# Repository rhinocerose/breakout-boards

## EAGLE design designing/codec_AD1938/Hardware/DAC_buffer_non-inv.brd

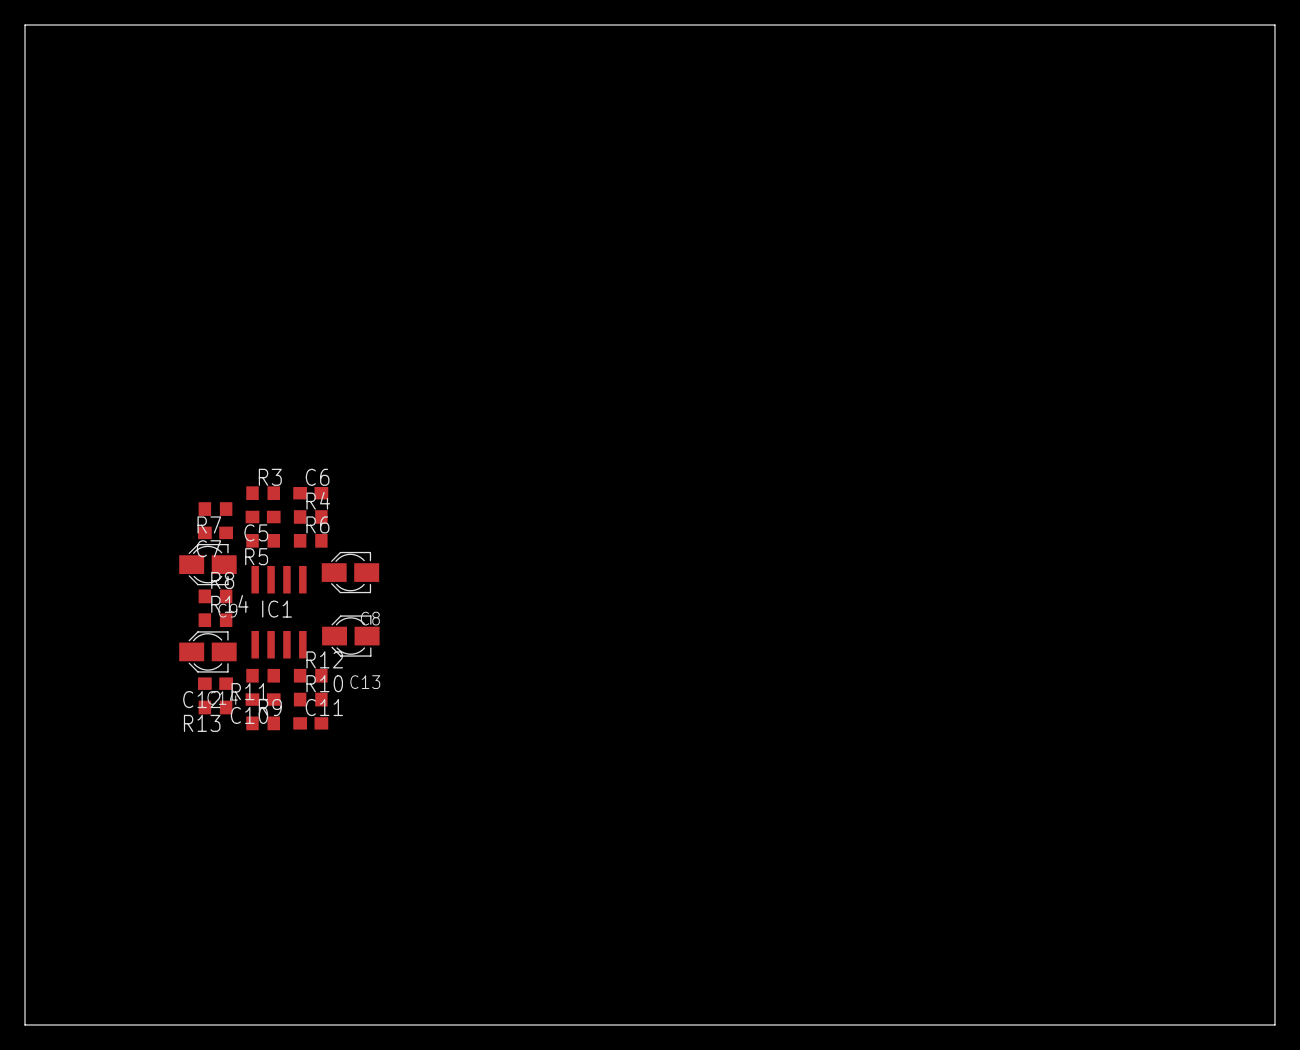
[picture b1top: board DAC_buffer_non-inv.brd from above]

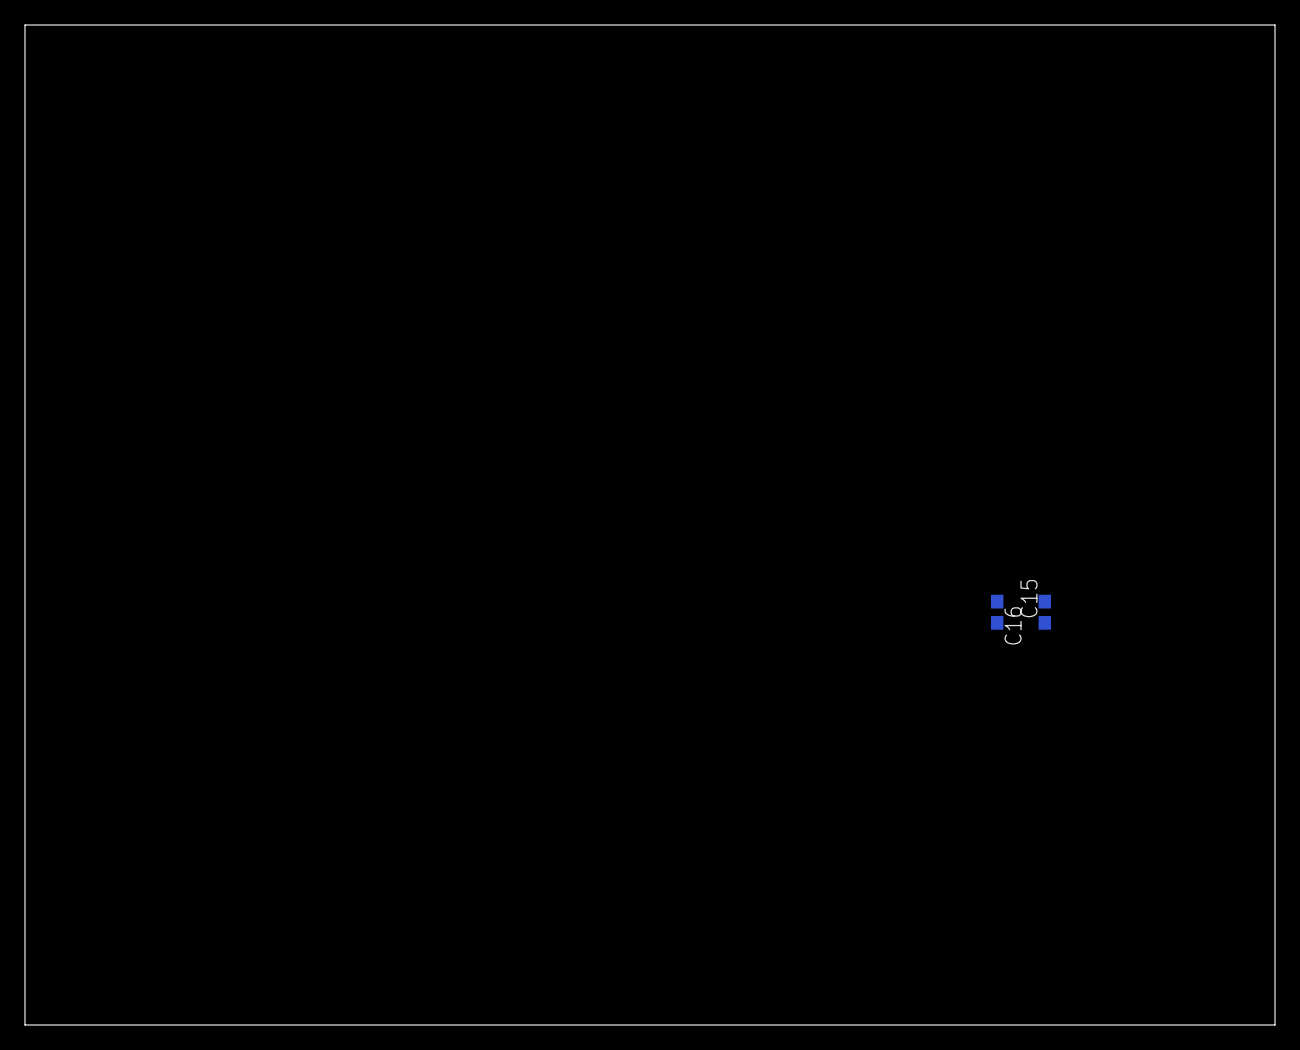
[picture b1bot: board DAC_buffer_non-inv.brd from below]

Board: 2 copper layers, 100.0 x 80.0 mm, 25 parts (2 on the bottom side), 17 nets, no tracks yet.

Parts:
C5, C10: 270pF; C0603
C6, C11: 430pF; C0603
C7, C12: 2.2nF; C0603
C8, C9, C13, C14: 47uF; PANASONIC_A
C15, C16: 100nF; C0603
IC1: TL072D; SO08
R3, R4, R5, R6, R9, R10, R11, R12: 4k75; R0603
R7, R13: 100R; R0603
R8, R14: R0603

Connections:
+12V: C15.2, IC1.8
-12V: C16.2, IC1.4
AGND: C6.1, C7.1, C8.-, C11.1, C12.1, C13.-, C15.1, C16.1, R8.1, R14.1
unnamed: C5.1, R3.2, R4.1
unnamed: C6.2, IC1.5, R4.2
unnamed: C5.2, IC1.7, R5.2, R7.1
unnamed: IC1.6, R5.1, R6.1
unnamed: C7.2, C9.+, R7.2
unnamed: C9.-, R8.2
unnamed: C8.+, R6.2
unnamed: C10.1, R9.2, R10.1
unnamed: C11.2, IC1.3, R10.2
unnamed: C10.2, IC1.1, R11.2, R13.1
unnamed: IC1.2, R11.1, R12.1
unnamed: C12.2, C14.+, R13.2
unnamed: C13.+, R12.2
unnamed: C14.-, R14.2

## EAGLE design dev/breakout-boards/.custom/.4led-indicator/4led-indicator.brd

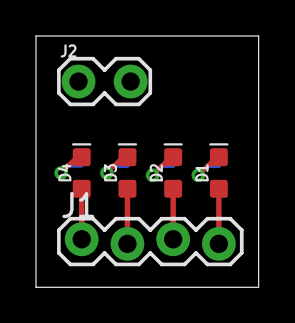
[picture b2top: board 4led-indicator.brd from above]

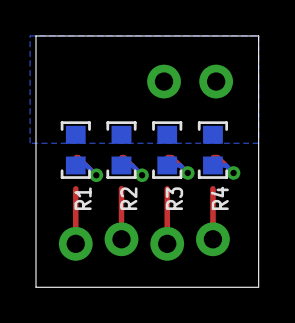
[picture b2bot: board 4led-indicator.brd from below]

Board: 2 copper layers, 12.4 x 14.0 mm, 10 parts (4 on the bottom side), 9 nets.

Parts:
D1, D2, D3, D4: LED-0603
J1: 1X04_LOCK
J2: 1X02_LOCK
R1, R2, R3, R4: R0603

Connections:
GND: J2.1, J2.2, R1.1, R2.1, R3.1, R4.1
unnamed: D1.A, J1.4
unnamed: D2.A, J1.3
unnamed: D3.A, J1.2
unnamed: D4.A, J1.1
unnamed: D1.C, R1.2
unnamed: D2.C, R2.2
unnamed: D3.C, R3.2
unnamed: D4.C, R4.2

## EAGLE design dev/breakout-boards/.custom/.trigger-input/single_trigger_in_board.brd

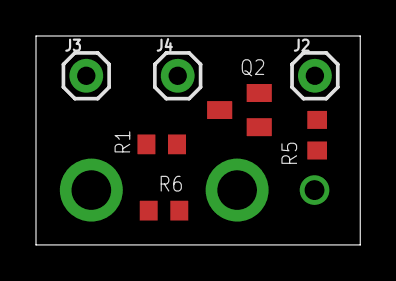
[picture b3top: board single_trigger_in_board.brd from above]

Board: 2 copper layers, 18.0 x 11.6 mm, 8 parts (1 on the bottom side), 5 nets, no tracks yet.

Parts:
J2, J3, J4: 1X01
Q2: MMBT3904LT1G; TRANSISTOR_SOT23-BEC
R1: 10k; R0603
R5: 1M; R0603
R6: 100k; R0603
TRIG1: KOBICONN_PJM301DM_JACK

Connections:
3V3_D: J3.1, R1.2
GND: J2.1, Q2.E, R5.2, TRIG1.P$2, TRIG1.P$3
unnamed: R6.2, TRIG1.P$1
unnamed: Q2.B, R5.1, R6.1
TR1: J4.1, Q2.C, R1.1

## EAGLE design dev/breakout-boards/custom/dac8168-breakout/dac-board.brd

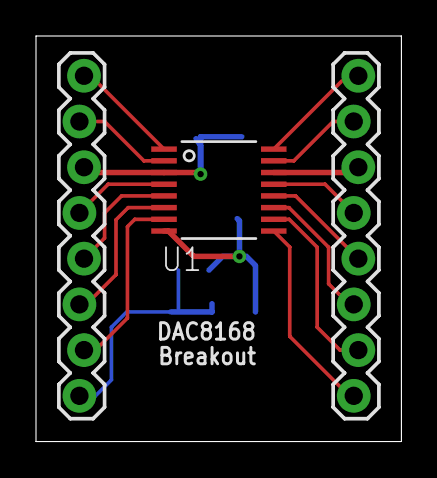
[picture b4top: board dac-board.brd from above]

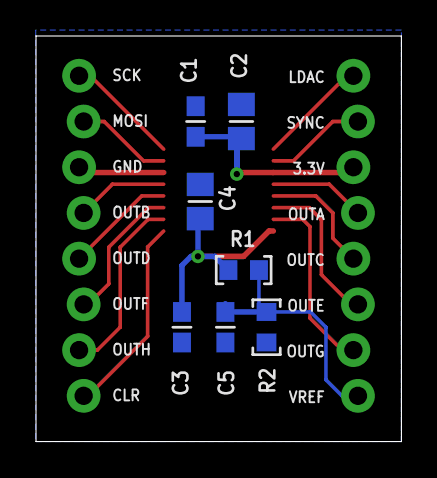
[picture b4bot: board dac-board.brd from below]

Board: 2 copper layers, 20.3 x 22.5 mm, 10 parts (7 on the bottom side), 17 nets.

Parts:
C1, C5: 100n; C0603
C2, C4: 2.2u; C0805
C3: 150n; C0603
J1, J2: 1X08_LOCK
R1, R2: R0603
U1: DAC8168ICPWPW16-L; PW16-L

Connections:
CLR: J2.1, U1.9
LDAC: J1.8, U1.1
MOSI: J2.7, U1.15
OUT_A: J1.5, U1.4
OUT_B: J2.5, U1.13
OUT_C: J1.4, U1.5
OUT_D: J2.4, U1.12
OUT_E: J1.3, U1.6
OUT_F: J2.3, U1.11
OUT_G: J1.2, U1.7
OUT_H: J2.2, U1.10
PE: C1.2, C2.2, C3.2, C4.2, C5.2, J2.6, R2.1, U1.14
SCK: J2.8, U1.16
SYNC: J1.7, U1.2
VDD: C1.1, C2.1, J1.6, U1.3
VREF: C3.1, C4.1, R1.2, U1.8
VREF_OUT: C5.1, J1.1, R1.1, R2.2

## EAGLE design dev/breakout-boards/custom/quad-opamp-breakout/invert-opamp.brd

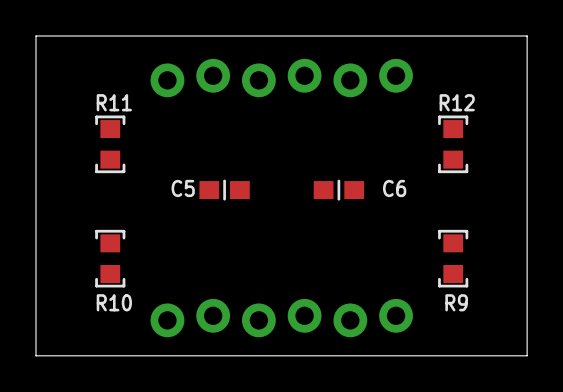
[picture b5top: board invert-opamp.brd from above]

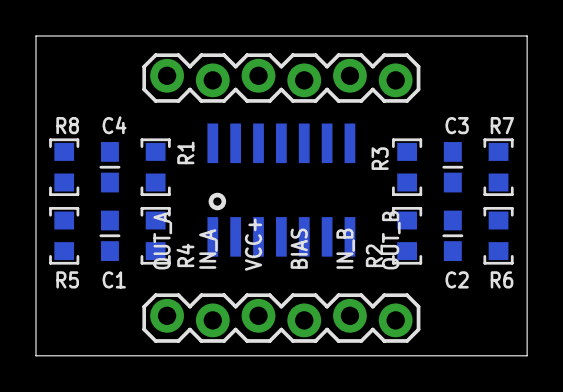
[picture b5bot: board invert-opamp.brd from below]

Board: 2 copper layers, 27.3 x 17.8 mm, 21 parts (15 on the bottom side), 20 nets, no tracks yet.

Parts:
C1, C2, C3, C4: 18pF; C0603
C5, C6: C0603
IC1: OPAMP-TL074D; SO14
J1, J2: 1X06_LOCK
R1, R2, R3, R4: 220R; R0603
R5, R6, R7, R8: 100k; R0603
R9, R10, R11, R12: 24k; R0603

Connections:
IN_A: J1.2, R9.1
IN_B: J1.5, R10.1
IN_C: J2.5, R11.1
IN_D: J2.2, R12.1
unnamed: C1.1, IC1.2, R5.1, R9.2
unnamed: IC1.1, R1.1
unnamed: IC1.8, R3.1
unnamed: C2.1, IC1.6, R6.1, R10.2
unnamed: IC1.7, R2.1
unnamed: C3.1, IC1.9, R7.1, R11.2
unnamed: C4.1, IC1.13, R8.1, R12.2
unnamed: IC1.14, R4.1
OUT_A: C1.2, J1.1, R1.2, R5.2
OUT_B: C2.2, J1.6, R2.2, R6.2
OUT_C: C3.2, J2.6, R3.2, R7.2
OUT_D: C4.2, J2.1, R4.2, R8.2
PE: C5.1, C6.2, J2.4
VCC+: C5.2, IC1.4, J1.3
VCC-: C6.1, IC1.11, J2.3
VREF: IC1.3, IC1.5, IC1.10, IC1.12, J1.4

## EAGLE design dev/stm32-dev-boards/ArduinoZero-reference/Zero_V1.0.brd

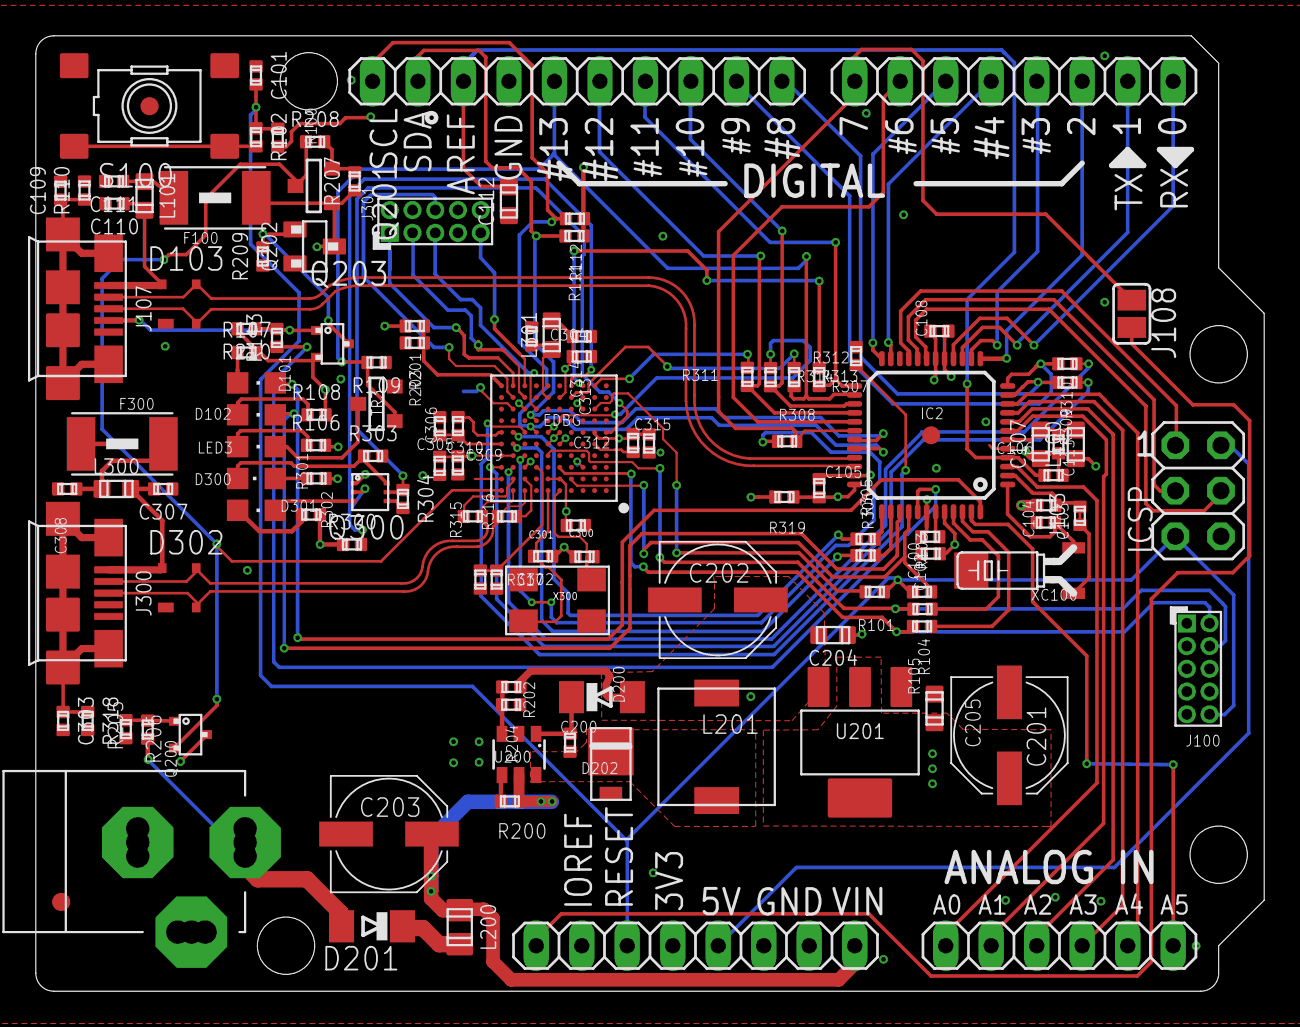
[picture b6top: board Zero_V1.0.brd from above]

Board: 4 copper layers, 68.6 x 53.3 mm, 129 parts (0 on the bottom side), 104 nets.

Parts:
C100, C101, C102, C105, C106, C108, C113, C304, C309, C311, C312, C313: 100nF; C0402
C103, C104: 6.8pF; C0402
C107: 10uF; C0603
C109, C303: DNP; C0402
C110, C111: 4.7nF; C0402
C112, C204, C205: 4.7uF; C0603
C200: 10n; C0402
C201, C203: 10uF; PANASONIC_D
C202: 47u; PANASONIC_D
C300, C301: 22pF; C0402
C302: 10pF; C0402
C305, C310: 1uF; C0402
C306, C307, C308: 1nF; C0402
C314, C315: 2.2uF; C0402
D101, D102, D301: Yellow; CHIPLED_0805
D103, D302: PRTR5V0U2XB; SOT143B
D200: CD1206-S01575; MINIMELF
D201: BYS10-45-E3; MINIMELF
D202: SS1P3L; DO220AAL
D300: Green; CHIPLED_0805
EDBG: VFBGA100
F100: MF-MSMF050-2; WUERTH-ELEKTRONIK_1812
F300: WUERTH-ELEKTRONIK_1812
FD1, FD2: FIDUCIALMOUNT; FIDUCIA-MOUNT
IC2: SAMD21G18A-AUT; TQFP48
ICSP: 3x2 M; 2X03
J100, J301: PINHEAD-2x5-P1.27; PINHEAD_2X05_127
J101: FH254-110DF08500V; 1X10
J102, J105: FH254-108DF08500V; 1X08
J103: C0402
J106: FH254-106DF08500V; 1X06
J107, J300: ZX62-AB-5PA; USB-MICRO-10103594
J108: SJ
J200: POWER-SUPPLY; POWERSUPPLY_DC-21MM
L100, L101, L300, L301: BLM18PG471SN1; C0603
L200: MH2029-300Y; C0805
L201: 10uH-SRR0604-100ML; SRR0604
LED3: Yellow; CHIPLED_0805
Q200, Q203: IRLML6402PBF; SOT323
Q201: IRLML6402PBF; SOT-23
Q202: 2N7002; SOT23
Q300: 2N7002DW-7-FNO_PAD; PWR_SC70-6L2
R100, R200, R204: 10k; C0402
R101, R103, R106, R107, R108, R109, R113, R301, R302, R305, R306, R307, R308, R309, R310, R311, R312, R313, R314: 330R; C0402
R102, R315, R316: 39R; C0402
R104, R105, R319: 0R; C0402
R110, R111, R112, R208, R303, R318: DNP; C0402
R201, R203: 47k; C0402
R202: 52.3k; C0402
R205, R206, R209, R210: 100k; C0402
R207, R300, R304: 1M; C0402
R317: 6.8k; C0402
S100: PUSHBUTTON3; TS42_4PINS
TP300, TP301: TP_SP; TP-SP
TR3: Q100; SOT-23
U200: LM2734Y; SOT23-6
U201: LDO-TS1117CW-3V3; SOT223
U$5: DNP; FRAME
X300: 12mHz-12pF-K7; CRYSTAL-5.4-3.2
XC100: 32.768kHz; CRYSTAL_TC26SMD

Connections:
+3V3: C100.1, C105.1, C108.2, C201.+, C205.2, IC2.17, IC2.36, IC2.44, J100.1, J105.2, J105.4, L100.2, Q203.3, R100.2, R106.1, R107.1, R108.1, R111.2, R112.2, R201.2, R210.1, R319.1, U201.2, U201.4
+5V: C202.+, C204.1, D200.A, F100.2, ICSP.2, J105.5, L201.P$2, Q200.2, Q201.3, Q202.3, R202.1, R207.2, U201.3
ATN: J105.1, J108.2
BD_N: D302.3, EDBG.A9, J300.D-, R315.1
BD_P: D302.2, EDBG.A8, J300.D+, R316.1
BOOST: C200.1, D200.C, U200.1
DGI_GPIO1: IC2.30, J102.8, J108.1, R308.1
DGI_GPIO2: IC2.11, J101.1, R309.1
DGI_GPIO3: IC2.12, J101.2, R310.1
EDBG_ADC0: EDBG.K10, R201.1, R203.2
EDBG_FORCE_BOOT: EDBG.H9, TP301.X
EDBG_JTAG_TCK: EDBG.K9, J301.1
EDBG_JTAG_TDI: EDBG.K8, J301.9
EDBG_JTAG_TDO: EDBG.J8, J301.3
EDBG_JTAG_TMS: EDBG.H7, J301.5
EDBG_RESET_N: EDBG.J9, J301.6
EN: R200.2, U200.4
FB: R202.2, R204.1, U200.3
GND: C100.2, C101.2, C102.2, C103.1, C104.1, C105.2, C106.2, C107.2, C108.1, C109.1, C110.1, C111.1, C112.2, C113.2, C201.-, C202.-, C203.-, C204.2, C205.1, C300.2, C301.2, C302.2, C303.1, C304.2, C305.2, C306.2, C307.2, C308.2, C309.2, C310.2, C311.2, C312.2, C313.2, C314.2, C315.2, D103.1, D202.P$2, D302.1, EDBG.B10, EDBG.C3, EDBG.C8, EDBG.E2, EDBG.E6, EDBG.F5, EDBG.F10, EDBG.H3, EDBG.H8, IC2.5, IC2.18, IC2.35, IC2.42, ICSP.6, J100.3, J100.5, J100.9, J101.7, J105.6, J105.7, J107.GND, J200.1, J200.3, J300.GND, J301.2, J301.10, Q202.2, Q300.1, Q300.4, R109.2, R110.1, R203.1, R204.2, R206.1, R209.2, R303.1, R304.1, R317.1, R318.1, S100.1, S100.2, TP300.X, TR3.2, U200.2, U201.1, XC100.P$1
MISO: IC2.28, J101.5, R311.2
MOSI: IC2.25, J101.4, R312.2
unnamed: D300.C, Q300.6, R303.2
unnamed: D301.C, Q300.3
unnamed: LED3.C, TR3.1
unnamed: R102.1, S100.3, S100.4
unnamed: C303.2, J300.SHLD1, J300.SHLD2, J300.SHLD3, J300.SHLD4, J300.SHLD5, J300.SHLD6, R318.2
unnamed: Q201.2, R207.1, R208.1
unnamed: C110.2, D103.4, J107.VBUS, L101.1
unnamed: D201.C, L200.1
unnamed: Q202.1, Q203.2, R209.1
unnamed: C106.1, C107.1, IC2.6, L100.1
unnamed: C109.2, J107.SHLD1, J107.SHLD2, J107.SHLD3, J107.SHLD4, J107.SHLD5, J107.SHLD6, R110.2
unnamed: C111.2, F100.1, L101.2
unnamed: C308.1, F300.1, L300.2
unnamed: EDBG.B9, R315.2
unnamed: EDBG.B8, R316.2
unnamed: D102.A, R108.2
unnamed: D101.A, R107.2
unnamed: LED3.A, R106.2
unnamed: C302.1, EDBG.C7, R317.2
unnamed: C301.1, EDBG.A6, X300.1
unnamed: C300.1, EDBG.A5, X300.3
unnamed: C305.1, C306.1, EDBG.E10
unnamed: C304.1, EDBG.J6, L301.2
unnamed: EDBG.K2, R311.1
unnamed: EDBG.K3, R312.1
unnamed: EDBG.J4, R313.1
unnamed: EDBG.G5, R314.1
unnamed: EDBG.C9, R310.2
unnamed: EDBG.C10, R309.2
unnamed: EDBG.D8, R308.2
unnamed: EDBG.F8, R307.2
unnamed: EDBG.E9, R306.2
unnamed: EDBG.F9, R305.2
unnamed: D300.A, R301.1
unnamed: D301.A, R302.1
PA00_XIN32: C103.2, IC2.1, XC100.2
PA01_XOUT32: C104.2, IC2.2, J103.1, J103.2, XC100.1
PA02_AIN0: IC2.3, J106.1
PA03_AREFA: C112.1, C113.1, IC2.4, J101.8
PA04_AIN4: IC2.9, J106.4
PA05_AIN5: IC2.10, J106.5
PA08_TCC0-W0: IC2.23, J102.5
PA09_TCC0-W1: IC2.14, J102.4
PA10_TCC0-W2: IC2.15, J102.2
PA11_TCC0-W3: IC2.16, J102.1
PA14_TCC0-W4: IC2.13, J102.3
PA15_TCC0-W5: IC2.24, J102.6
PA20_TCC0-W6: IC2.29, J102.7
PA27_TX_LED: D102.C, IC2.39
PA28_USB_HOST_EN: IC2.41, R113.2
PA30_SWCLK: IC2.45, R104.1
PA31_SWDIO: IC2.46, R105.2
PB02_AIN10: IC2.47, J106.6
PB03_RX_LED: D101.C, IC2.48
PB08_AIN2: IC2.7, J106.2
PB09_AIN3: IC2.8, J106.3
PB10_S4_SPI_MOSI: IC2.19, ICSP.4
PB11_S4_SPI_SCK: IC2.20, ICSP.3
PB12_S4_SPI_MISO: IC2.21, ICSP.1
POWER_LED_CTRL: EDBG.K4, Q300.2, R300.1
RXD: IC2.38, R306.1
SAMD21_RESET: EDBG.B4, IC2.40, R103.1
SCK: IC2.26, J101.6, R109.1, R313.2, TR3.3
SCL: EDBG.F7, IC2.32, J101.10, R112.1
SDA: EDBG.G7, IC2.31, J101.9, R111.1
SS: IC2.27, J101.3, R314.2
STATUS_LED_CTRL: EDBG.F1, Q300.5, R304.2
SW: C200.2, D202.P$1, L201.P$1, U200.6
SWCLK: EDBG.D6, J100.4, R104.2
SWDIO: EDBG.C5, J100.2, R105.1
TARGET_RESET: C101.1, ICSP.5, J100.10, J105.3, R100.1, R101.2, R102.2, R103.2
TARGET_RESET_SENSE: EDBG.H2, R101.1
TARGET_USB_N: D103.3, IC2.33, J107.D-
TARGET_USB_P: D103.2, IC2.34, J107.D+
TXD: IC2.37, R305.1
USB_HOST_ENABLE: J107.ID, Q203.1, R113.1, R210.2
VCC_EDBG_3V3: C309.1, C310.1, C311.1, C312.1, C313.1, C314.1, C315.1, EDBG.B5, EDBG.B6, EDBG.D9, EDBG.D10, EDBG.E5, EDBG.F2, EDBG.F6, EDBG.J5, J301.4, L301.1, R300.2, R301.2, R302.2, R319.2
VCC_EDBG_USB: EDBG.A10, F300.2, Q200.3, Q201.1, R208.2
VCC_EXT_VIN: C203.+, J105.8, L200.2, R200.1, U200.5
VDDCORE: C102.1, IC2.43
VEXT: D201.A, J200.2, R205.2
VIN_DETECT: Q200.1, R205.1, R206.2
XVCC: C307.1, D302.4, J300.VBUS, L300.1

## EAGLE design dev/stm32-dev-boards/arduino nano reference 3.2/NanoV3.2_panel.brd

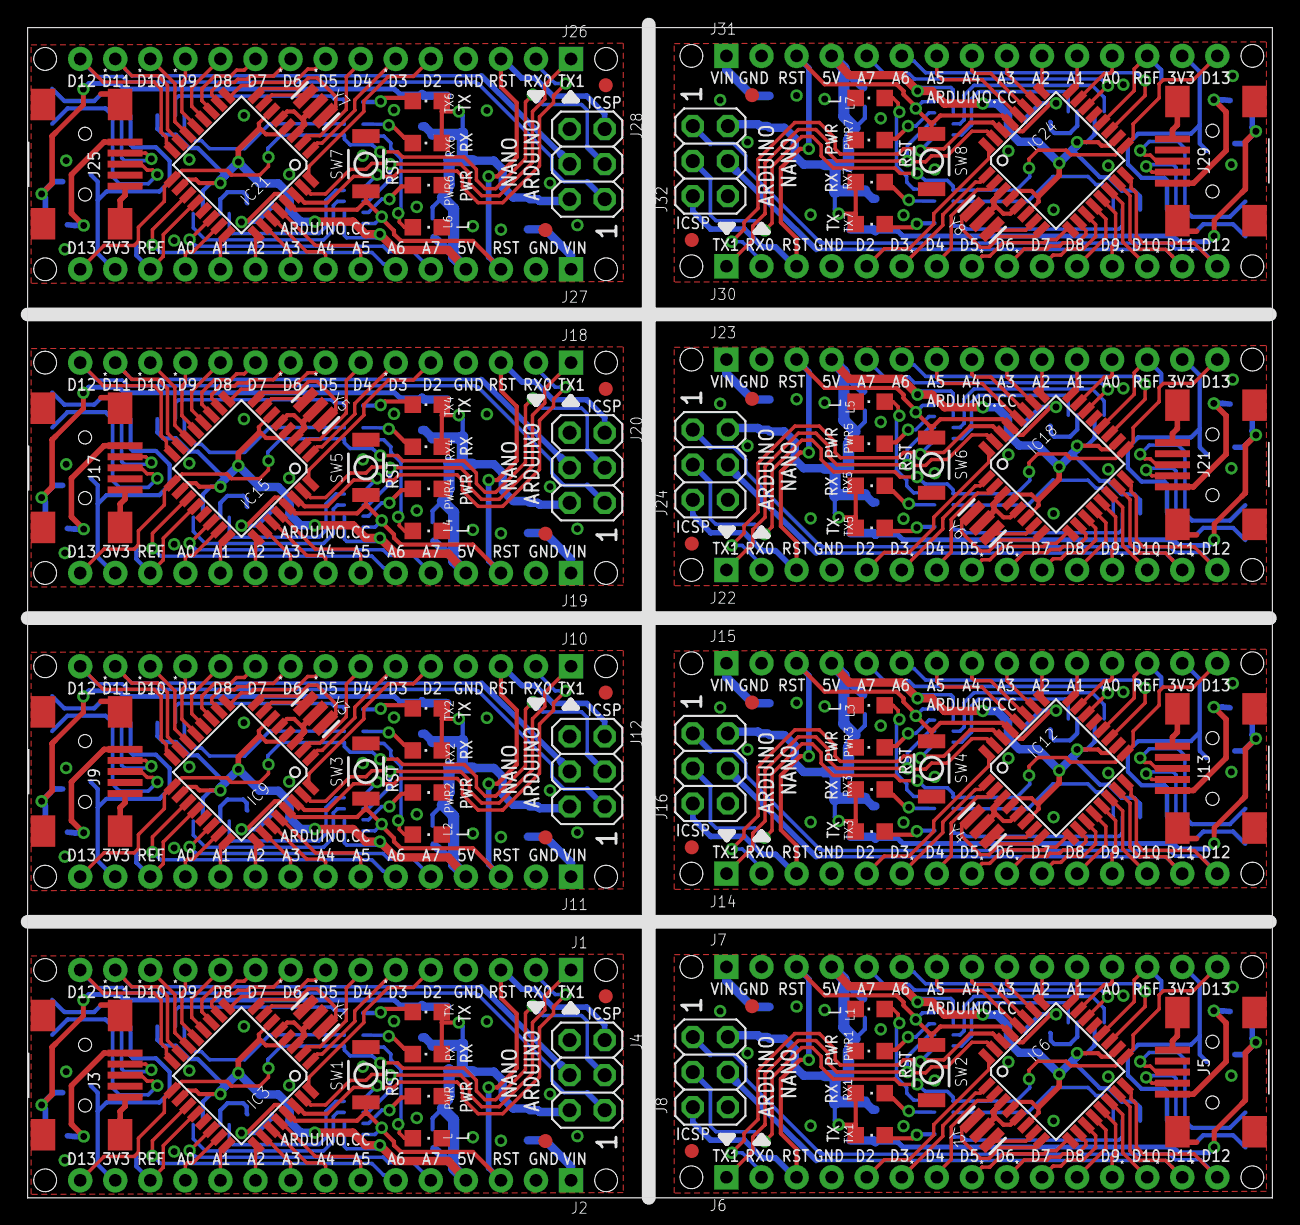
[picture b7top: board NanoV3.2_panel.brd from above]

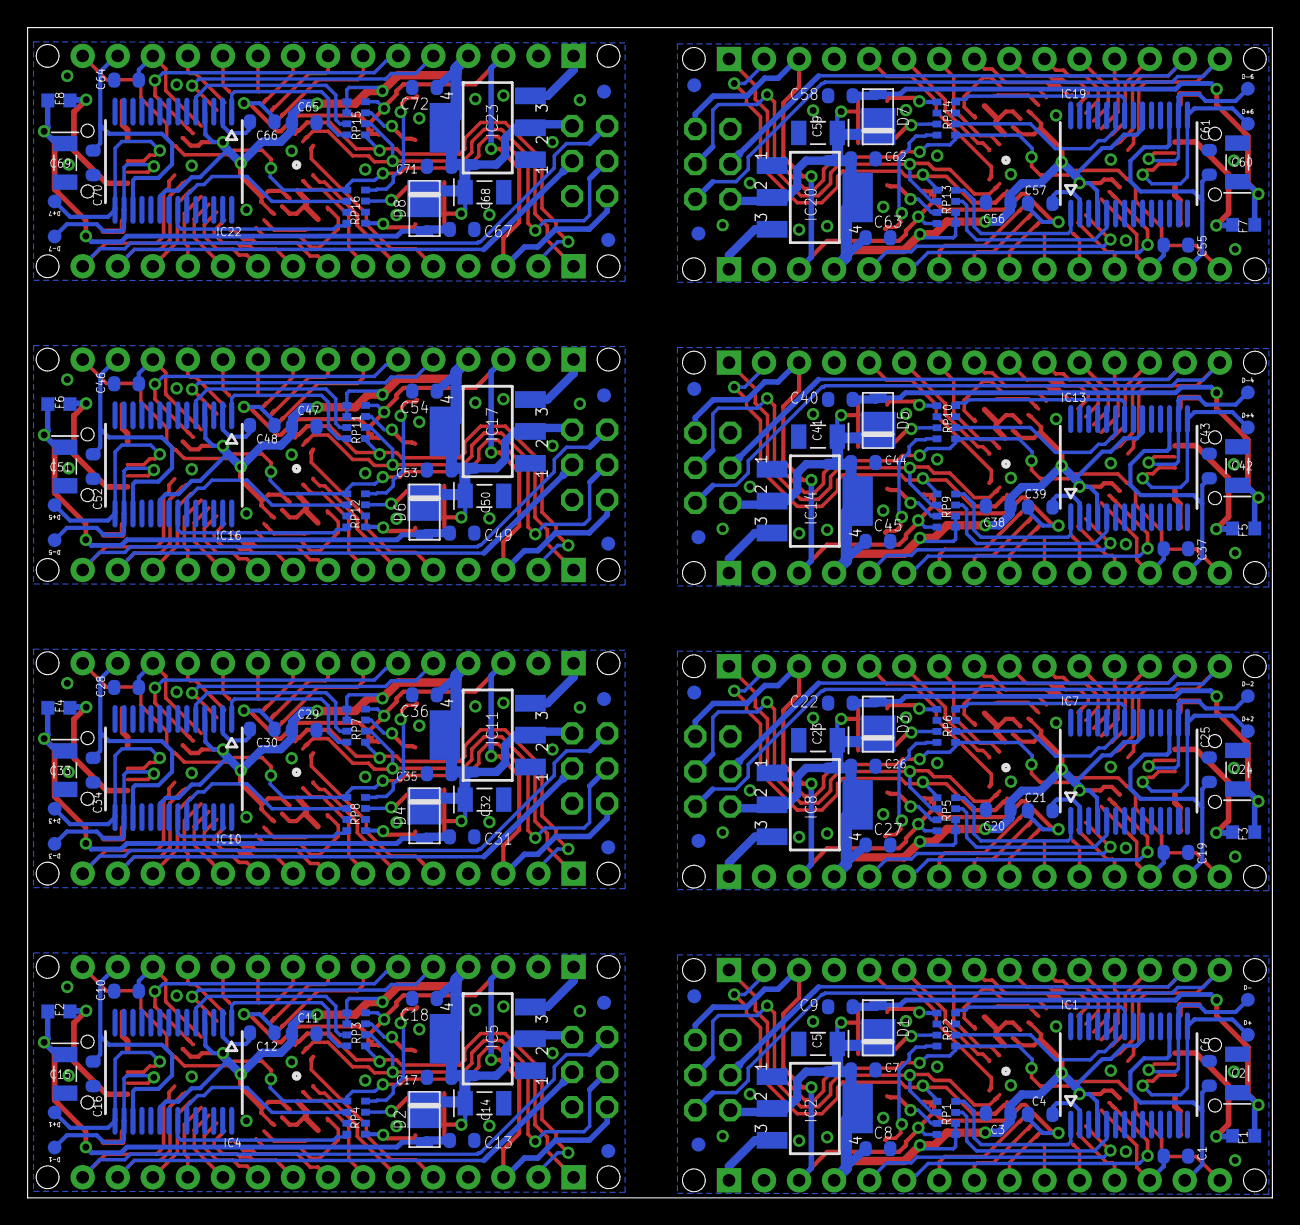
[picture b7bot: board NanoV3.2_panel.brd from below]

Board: 2 copper layers, 90.2 x 84.8 mm, 256 parts (136 on the bottom side), 344 nets.

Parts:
C1, C4, C6, C9, C10, C12, C13, C16, C19, C21, C22, C25, C28, C30, C31, C34, C37, C39, C40, C43, C46, C48, C49, C52, C55, C57, C58, C61, C64, C66, C67, C70: 100nF; C0603-ROUND
C2, C5, C14, C15, C23, C24, C32, C33, C41, C42, C50, C51, C59, C60, C68, C69: 4,7uF_16V; TAN-A
C3, C7, C8, C11, C17, C18, C20, C26, C27, C29, C35, C36, C38, C44, C45, C47, C53, C54, C56, C62, C63, C65, C71, C72: 1uF; C0603-ROUND
D1, D2, D3, D4, D5, D6, D7, D8: SS1P3L; DO220AAL
D+, D+1, D+2, D+3, D+4, D+5, D+6, D+7: DNP; TP-1.00MM
D-, D-1, D-2, D-3, D-4, D-5, D-6, D-7: DNP; TP-1.00MM
F1, F2, F3, F4, F5, F6, F7, F8: MFFSMF050; 0603-1608X90N
IC1, IC4, IC7, IC10, IC13, IC16, IC19, IC22: FT232RL; SSOP28
IC2, IC5, IC8, IC11, IC14, IC17, IC20, IC23: LM1117IMPX-5.0; LINEAR_SOT223
IC3, IC6, IC9, IC12, IC15, IC18, IC21, IC24: ATMEGA328P-AU; TQFP32-08
J1, J2, J6, J7, J10, J11, J14, J15, J18, J19, J22, J23, J26, J27, J30, J31: XXXX_STRIPNANO; HEAD15-NOSS
J3, J5, J9, J13, J17, J21, J25, J29: USB-MINI-B_2
J4, J8, J12, J16, J20, J24, J28, J32: 2X03
L, L1, L2, L3, L4, L5, L6, L7: Yellow; CHIPLED_0805
PWR, PWR1, PWR2, PWR3, PWR4, PWR5, PWR6, PWR7: Green; CHIPLED_0805
RP1, RP2, RP3, RP4, RP5, RP6, RP7, RP8, RP9, RP10, RP11, RP12, RP13, RP14, RP15, RP16: 1K; CAY16
RX, RX1, RX2, RX3, RX4, RX5, RX6, RX7: Red; CHIPLED_0805
SW1, SW2, SW3, SW4, SW5, SW6, SW7, SW8: RESET; SMD_157SW
TX, TX1, TX2, TX3, TX4, TX5, TX6, TX7: Green; CHIPLED_0805
U$1, U$2, U$3, U$4, U$5, U$6, U$7, U$8, U$9, U$10, U$11, U$12, U$13, U$14, U$15, U$16, U$17, U$18, U$19, U$20, U$21, U$22, U$23, U$24, U$25, U$26, U$27, U$28, U$29, U$30, U$53, U$54: DNP; FD-1-1.5
Y1, Y2, Y3, Y4, Y5, Y6, Y7, Y8: 16MHz; RESONATOR

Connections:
3V1: C16.2, IC4.17, J7.14
3V2: C25.2, IC7.17, J11.14
3V3: C6.2, IC1.17, J2.14
3V4: C34.2, IC10.17, J15.14
3V5: C43.2, IC13.17, J19.14
3V6: C52.2, IC16.17, J23.14
3V7: C61.2, IC19.17, J27.14
3V8: C70.2, IC22.17, J31.14
+5V: C3.1, C5.1, C7.1, C8.1, D1.P$1, IC1.4, IC1.20, IC2.2, IC2.4, IC3.4, IC3.6, IC3.18, J2.4, J4.2, RP1.5, RP1.6, RX.A, TX.A
+5V1: C11.1, C14.1, C17.1, C18.1, D2.P$1, IC4.4, IC4.20, IC5.2, IC5.4, IC6.4, IC6.6, IC6.18, J7.4, J8.2, RP3.5, RP3.6, RX1.A, TX1.A
+5V2: C20.1, C23.1, C26.1, C27.1, D3.P$1, IC7.4, IC7.20, IC8.2, IC8.4, IC9.4, IC9.6, IC9.18, J11.4, J12.2, RP5.5, RP5.6, RX2.A, TX2.A
+5V3: C29.1, C32.1, C35.1, C36.1, D4.P$1, IC10.4, IC10.20, IC11.2, IC11.4, IC12.4, IC12.6, IC12.18, J15.4, J16.2, RP7.5, RP7.6, RX3.A, TX3.A
+5V4: C38.1, C41.1, C44.1, C45.1, D5.P$1, IC13.4, IC13.20, IC14.2, IC14.4, IC15.4, IC15.6, IC15.18, J19.4, J20.2, RP9.5, RP9.6, RX4.A, TX4.A
+5V5: C47.1, C50.1, C53.1, C54.1, D6.P$1, IC16.4, IC16.20, IC17.2, IC17.4, IC18.4, IC18.6, IC18.18, J23.4, J24.2, RP11.5, RP11.6, RX5.A, TX5.A
+5V6: C56.1, C59.1, C62.1, C63.1, D7.P$1, IC19.4, IC19.20, IC20.2, IC20.4, IC21.4, IC21.6, IC21.18, J27.4, J28.2, RP13.5, RP13.6, RX6.A, TX6.A
+5V7: C65.1, C68.1, C71.1, C72.1, D8.P$1, IC22.4, IC22.20, IC23.2, IC23.4, IC24.4, IC24.6, IC24.18, J31.4, J32.2, RP15.5, RP15.6, RX7.A, TX7.A
A0: IC3.23, J2.12
A1: IC3.24, J2.11
A2: IC3.25, J2.10
A3: IC3.26, J2.9
A4: IC3.27, J2.8
A5: IC3.28, J2.7
A6: IC3.19, J2.6
A7: IC3.22, J2.5
A8: IC6.26, J7.9
A9: IC6.25, J7.10
A10: IC6.24, J7.11
A11: IC6.23, J7.12
A12: IC6.27, J7.8
A13: IC6.28, J7.7
A14: IC6.19, J7.6
A15: IC6.22, J7.5
A16: IC9.26, J11.9
A17: IC9.25, J11.10
A18: IC9.24, J11.11
A19: IC9.23, J11.12
A20: IC9.27, J11.8
A21: IC9.28, J11.7
A22: IC9.19, J11.6
A23: IC9.22, J11.5
A24: IC12.26, J15.9
A25: IC12.25, J15.10
A26: IC12.24, J15.11
A27: IC12.23, J15.12
A28: IC12.27, J15.8
A29: IC12.28, J15.7
A30: IC12.19, J15.6
A31: IC12.22, J15.5
A32: IC15.26, J19.9
A33: IC15.25, J19.10
A34: IC15.24, J19.11
A35: IC15.23, J19.12
A36: IC15.27, J19.8
A37: IC15.28, J19.7
A38: IC15.19, J19.6
A39: IC15.22, J19.5
A40: IC18.26, J23.9
A41: IC18.25, J23.10
A42: IC18.24, J23.11
A43: IC18.23, J23.12
A44: IC18.27, J23.8
A45: IC18.28, J23.7
A46: IC18.19, J23.6
A47: IC18.22, J23.5
A48: IC21.26, J27.9
A49: IC21.25, J27.10
A50: IC21.24, J27.11
A51: IC21.23, J27.12
A52: IC21.27, J27.8
A53: IC21.28, J27.7
A54: IC21.19, J27.6
A55: IC21.22, J27.5
A56: IC24.26, J31.9
A57: IC24.25, J31.10
A58: IC24.24, J31.11
A59: IC24.23, J31.12
A60: IC24.27, J31.8
A61: IC24.28, J31.7
A62: IC24.19, J31.6
A63: IC24.22, J31.5
AREF: C1.1, IC3.20, J2.13
AREF1: C10.1, IC6.20, J7.13
AREF2: C19.1, IC9.20, J11.13
AREF3: C28.1, IC12.20, J15.13
AREF4: C37.1, IC15.20, J19.13
AREF5: C46.1, IC18.20, J23.13
AREF6: C55.1, IC21.20, J27.13
AREF7: C64.1, IC24.20, J31.13
COM: C1.2, C2.2, C3.2, C5.2, C6.1, C7.2, C8.2, C9.2, IC1.7, IC1.18, IC1.21, IC1.25, IC1.26, IC2.1, IC3.3, IC3.5, IC3.21, J1.4, J2.2, J3.1, J3.6, J3.7, J3.8, J3.9, J4.6, L.C, PWR.C, RP2.3, RP2.6, SW1.1, Y1.2
COM1: C10.2, C11.2, C13.2, C14.2, C15.2, C16.1, C17.2, C18.2, IC4.7, IC4.18, IC4.21, IC4.25, IC4.26, IC5.1, IC6.3, IC6.5, IC6.21, J5.1, J5.6, J5.7, J5.8, J5.9, J6.4, J7.2, J8.6, L1.C, PWR1.C, RP4.3, RP4.6, SW2.1, Y2.2
COM2: C19.2, C20.2, C22.2, C23.2, C24.2, C25.1, C26.2, C27.2, IC7.7, IC7.18, IC7.21, IC7.25, IC7.26, IC8.1, IC9.3, IC9.5, IC9.21, J9.1, J9.6, J9.7, J9.8, J9.9, J10.4, J11.2, J12.6, L2.C, PWR2.C, RP6.3, RP6.6, SW3.1, Y3.2
COM3: C28.2, C29.2, C31.2, C32.2, C33.2, C34.1, C35.2, C36.2, IC10.7, IC10.18, IC10.21, IC10.25, IC10.26, IC11.1, IC12.3, IC12.5, IC12.21, J13.1, J13.6, J13.7, J13.8, J13.9, J14.4, J15.2, J16.6, L3.C, PWR3.C, RP8.3, RP8.6, SW4.1, Y4.2
COM4: C37.2, C38.2, C40.2, C41.2, C42.2, C43.1, C44.2, C45.2, IC13.7, IC13.18, IC13.21, IC13.25, IC13.26, IC14.1, IC15.3, IC15.5, IC15.21, J17.1, J17.6, J17.7, J17.8, J17.9, J18.4, J19.2, J20.6, L4.C, PWR4.C, RP10.3, RP10.6, SW5.1, Y5.2
COM5: C46.2, C47.2, C49.2, C50.2, C51.2, C52.1, C53.2, C54.2, IC16.7, IC16.18, IC16.21, IC16.25, IC16.26, IC17.1, IC18.3, IC18.5, IC18.21, J21.1, J21.6, J21.7, J21.8, J21.9, J22.4, J23.2, J24.6, L5.C, PWR5.C, RP12.3, RP12.6, SW6.1, Y6.2
COM6: C55.2, C56.2, C58.2, C59.2, C60.2, C61.1, C62.2, C63.2, IC19.7, IC19.18, IC19.21, IC19.25, IC19.26, IC20.1, IC21.3, IC21.5, IC21.21, J25.1, J25.6, J25.7, J25.8, J25.9, J26.4, J27.2, J28.6, L6.C, PWR6.C, RP14.3, RP14.6, SW7.1, Y7.2
COM7: C64.2, C65.2, C67.2, C68.2, C69.2, C70.1, C71.2, C72.2, IC22.7, IC22.18, IC22.21, IC22.25, IC22.26, IC23.1, IC24.3, IC24.5, IC24.21, J29.1, J29.6, J29.7, J29.8, J29.9, J30.4, J31.2, J32.6, L7.C, PWR7.C, RP16.3, RP16.6, SW8.1, Y8.2
D0/RX: IC3.30, J1.2, RP1.1
D0/RX1: IC6.30, J6.2, RP3.1
D0/RX2: IC9.30, J10.2, RP5.1
D0/RX3: IC12.30, J14.2, RP7.1
D0/RX4: IC15.30, J18.2, RP9.1
D0/RX5: IC18.30, J22.2, RP11.1
D0/RX6: IC21.30, J26.2, RP13.1
D0/RX7: IC24.30, J30.2, RP15.1
D1: IC6.9, J6.8
D1/TX: IC3.31, J1.1, RP1.2
D1/TX1: IC6.31, J6.1, RP3.2
D1/TX2: IC9.31, J10.1, RP5.2
D1/TX3: IC12.31, J14.1, RP7.2
D1/TX4: IC15.31, J18.1, RP9.2
D1/TX5: IC18.31, J22.1, RP11.2
D1/TX6: IC21.31, J26.1, RP13.2
D1/TX7: IC24.31, J30.1, RP15.2
D2: IC3.32, J1.5
D3: IC3.1, J1.6
D4: IC3.2, J1.7
D5: IC3.9, J1.8
D6: IC3.10, J1.9
D7: IC3.11, J1.10
D8: IC3.12, J1.11
D9: IC3.13, J1.12
D10: IC3.14, J1.13
D11: IC6.2, J6.7
D11/MOSI: IC3.15, J1.14, J4.4
D11/MOSI1: IC6.15, J6.14, J8.4
D11/MOSI2: IC9.15, J10.14, J12.4
D11/MOSI3: IC12.15, J14.14, J16.4
D11/MOSI4: IC15.15, J18.14, J20.4
D11/MOSI5: IC18.15, J22.14, J24.4
D11/MOSI6: IC21.15, J26.14, J28.4
D11/MOSI7: IC24.15, J30.14, J32.4
D12: IC6.1, J6.6
D12/MISO: IC3.16, J1.15, J4.1
D12/MISO1: IC6.16, J6.15, J8.1
D12/MISO2: IC9.16, J10.15, J12.1
D12/MISO3: IC12.16, J14.15, J16.1
D12/MISO4: IC15.16, J18.15, J20.1
D12/MISO5: IC18.16, J22.15, J24.1
D12/MISO6: IC21.16, J26.15, J28.1
D12/MISO7: IC24.16, J30.15, J32.1
D13: IC6.32, J6.5
D13/SCK: IC3.17, J2.15, J4.3, RP2.1
D13/SCK1: IC6.17, J7.15, J8.3, RP4.1
D13/SCK2: IC9.17, J11.15, J12.3, RP6.1
D13/SCK3: IC12.17, J15.15, J16.3, RP8.1
D13/SCK4: IC15.17, J19.15, J20.3, RP10.1
D13/SCK5: IC18.17, J23.15, J24.3, RP12.1
D13/SCK6: IC21.17, J27.15, J28.3, RP14.1
D13/SCK7: IC24.17, J31.15, J32.3, RP16.1
D14: IC6.10, J6.9
D15: IC6.11, J6.10
D16: IC6.12, J6.11
D17: IC6.13, J6.12
D18: IC6.14, J6.13
D19: IC9.9, J10.8
D20: IC9.2, J10.7
D21: IC9.1, J10.6
D22: IC9.32, J10.5
D23: IC9.10, J10.9
D24: IC9.11, J10.10
D25: IC9.12, J10.11
D26: IC9.13, J10.12
D27: IC9.14, J10.13
D28: IC12.9, J14.8
D29: IC12.2, J14.7
D30: IC12.1, J14.6
D31: IC12.32, J14.5
D32: IC12.10, J14.9
D33: IC12.11, J14.10
D34: IC12.12, J14.11
D35: IC12.13, J14.12
D36: IC12.14, J14.13
D37: IC15.9, J18.8
D38: IC15.2, J18.7
D39: IC15.1, J18.6
D40: IC15.32, J18.5
D41: IC15.10, J18.9
D42: IC15.11, J18.10
D43: IC15.12, J18.11
D44: IC15.13, J18.12
D45: IC15.14, J18.13
D46: IC18.9, J22.8
D47: IC18.2, J22.7
D48: IC18.1, J22.6
D49: IC18.32, J22.5
D50: IC18.10, J22.9
D51: IC18.11, J22.10
D52: IC18.12, J22.11
D53: IC18.13, J22.12
D54: IC18.14, J22.13
D55: IC21.9, J26.8
D56: IC21.2, J26.7
D57: IC21.1, J26.6
D58: IC21.32, J26.5
D59: IC21.10, J26.9
D60: IC21.11, J26.10
D61: IC21.12, J26.11
D62: IC21.13, J26.12
D63: IC21.14, J26.13
D64: IC24.9, J30.8
D65: IC24.2, J30.7
D66: IC24.1, J30.6
D67: IC24.32, J30.5
D68: IC24.10, J30.9
D69: IC24.11, J30.10
D70: IC24.12, J30.11
D71: IC24.13, J30.12
D72: IC24.14, J30.13
unnamed: IC3.8, Y1.3
unnamed: IC3.7, Y1.1
unnamed: PWR.A, RP1.3
unnamed: C4.2, IC1.2
unnamed: D+.X, IC1.15, J3.3
unnamed: D-.X, IC1.16, J3.4
unnamed: L.A, RP2.8
unnamed: IC1.23, RP2.2
unnamed: IC1.22, RP2.4
unnamed: C12.2, IC4.2
unnamed: RP2.5, TX.C
unnamed: D+1.X, IC4.15, J5.3
unnamed: D-1.X, IC4.16, J5.4
unnamed: PWR1.A, RP3.3
unnamed: IC4.23, RP4.2
unnamed: IC4.22, RP4.4
unnamed: IC6.7, Y2.1
unnamed: IC6.8, Y2.3
unnamed: L1.A, RP4.8
unnamed: RP4.5, TX1.C
unnamed: F2.2, J5.5
unnamed: RP4.7, RX1.C
unnamed: C21.2, IC7.2
unnamed: D+2.X, IC7.15, J9.3
unnamed: D-2.X, IC7.16, J9.4
unnamed: F1.2, J3.5
unnamed: PWR2.A, RP5.3
unnamed: IC7.23, RP6.2
unnamed: RP2.7, RX.C
unnamed: IC7.22, RP6.4
unnamed: IC9.7, Y3.1
unnamed: IC9.8, Y3.3
unnamed: L2.A, RP6.8
unnamed: RP6.5, TX2.C
unnamed: F3.2, J9.5
unnamed: RP6.7, RX2.C
unnamed: C30.2, IC10.2
unnamed: D+3.X, IC10.15, J13.3
unnamed: D-3.X, IC10.16, J13.4
unnamed: PWR3.A, RP7.3
unnamed: IC10.23, RP8.2
unnamed: IC10.22, RP8.4
unnamed: IC12.7, Y4.1
unnamed: IC12.8, Y4.3
unnamed: L3.A, RP8.8
unnamed: RP8.5, TX3.C
unnamed: F4.2, J13.5
unnamed: RP8.7, RX3.C
unnamed: C39.2, IC13.2
unnamed: D+4.X, IC13.15, J17.3
unnamed: D-4.X, IC13.16, J17.4
unnamed: PWR4.A, RP9.3
unnamed: IC13.23, RP10.2
unnamed: IC13.22, RP10.4
unnamed: IC15.7, Y5.1
unnamed: IC15.8, Y5.3
unnamed: L4.A, RP10.8
unnamed: RP10.5, TX4.C
unnamed: F5.2, J17.5
unnamed: RP10.7, RX4.C
unnamed: C48.2, IC16.2
unnamed: D+5.X, IC16.15, J21.3
unnamed: D-5.X, IC16.16, J21.4
unnamed: PWR5.A, RP11.3
unnamed: IC16.23, RP12.2
unnamed: IC16.22, RP12.4
unnamed: IC18.7, Y6.1
unnamed: IC18.8, Y6.3
unnamed: L5.A, RP12.8
unnamed: RP12.5, TX5.C
unnamed: F6.2, J21.5
unnamed: RP12.7, RX5.C
unnamed: C57.2, IC19.2
unnamed: D+6.X, IC19.15, J25.3
unnamed: D-6.X, IC19.16, J25.4
unnamed: PWR6.A, RP13.3
unnamed: IC19.23, RP14.2
unnamed: IC19.22, RP14.4
unnamed: IC21.7, Y7.1
unnamed: IC21.8, Y7.3
unnamed: L6.A, RP14.8
unnamed: RP14.5, TX6.C
unnamed: F7.2, J25.5
unnamed: RP14.7, RX6.C
unnamed: C66.2, IC22.2
unnamed: D+7.X, IC22.15, J29.3
unnamed: D-7.X, IC22.16, J29.4
unnamed: PWR7.A, RP15.3
unnamed: IC22.23, RP16.2
unnamed: IC22.22, RP16.4
unnamed: IC24.7, Y8.1
unnamed: IC24.8, Y8.3
unnamed: L7.A, RP16.8
unnamed: RP16.5, TX7.C
unnamed: F8.2, J29.5
unnamed: RP16.7, RX7.C
RESET: C4.1, IC3.29, J1.3, J2.3, J4.5, RP1.4, SW1.2
RESET1: C12.1, IC6.29, J6.3, J7.3, J8.5, RP3.4, SW2.2
RESET2: C21.1, IC9.29, J10.3, J11.3, J12.5, RP5.4, SW3.2
RESET3: C30.1, IC12.29, J14.3, J15.3, J16.5, RP7.4, SW4.2
RESET4: C39.1, IC15.29, J18.3, J19.3, J20.5, RP9.4, SW5.2
RESET5: C48.1, IC18.29, J22.3, J23.3, J24.5, RP11.4, SW6.2
RESET6: C57.1, IC21.29, J26.3, J27.3, J28.5, RP13.4, SW7.2
RESET7: C66.1, IC24.29, J30.3, J31.3, J32.5, RP15.4, SW8.2
RX: IC1.1, RP1.8
RX1: IC4.1, RP3.8
RX2: IC7.1, RP5.8
RX3: IC10.1, RP7.8
RX4: IC13.1, RP9.8
RX5: IC16.1, RP11.8
RX6: IC19.1, RP13.8
RX7: IC22.1, RP15.8
TX: IC1.5, RP1.7
TX1: IC4.5, RP3.7
TX2: IC7.5, RP5.7
TX3: IC10.5, RP7.7
TX4: IC13.5, RP9.7
TX5: IC16.5, RP11.7
TX6: IC19.5, RP13.7
TX7: IC22.5, RP15.7
VIN: IC2.3, J2.1
VIN1: IC5.3, J7.1
VIN2: IC8.3, J11.1
VIN3: IC11.3, J15.1
VIN4: IC14.3, J19.1
VIN5: IC17.3, J23.1
VIN6: IC20.3, J27.1
VIN7: IC23.3, J31.1
VUSB: C2.1, C9.1, D1.P$2, F1.1
VUSB1: C13.1, C15.1, D2.P$2, F2.1
VUSB2: C22.1, C24.1, D3.P$2, F3.1
VUSB3: C31.1, C33.1, D4.P$2, F4.1
VUSB4: C40.1, C42.1, D5.P$2, F5.1
VUSB5: C49.1, C51.1, D6.P$2, F6.1
VUSB6: C58.1, C60.1, D7.P$2, F7.1
VUSB7: C67.1, C69.1, D8.P$2, F8.1

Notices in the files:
parts and their libraries:
SparkFun-LED: Licensing: Creative Commons ShareAlike 4.0 International - https://creativecommons.org/licenses/by-sa/4.0
Arduino-utility: Copyright (c) 2016-2017 Arduino LLC.  All right reserved.
